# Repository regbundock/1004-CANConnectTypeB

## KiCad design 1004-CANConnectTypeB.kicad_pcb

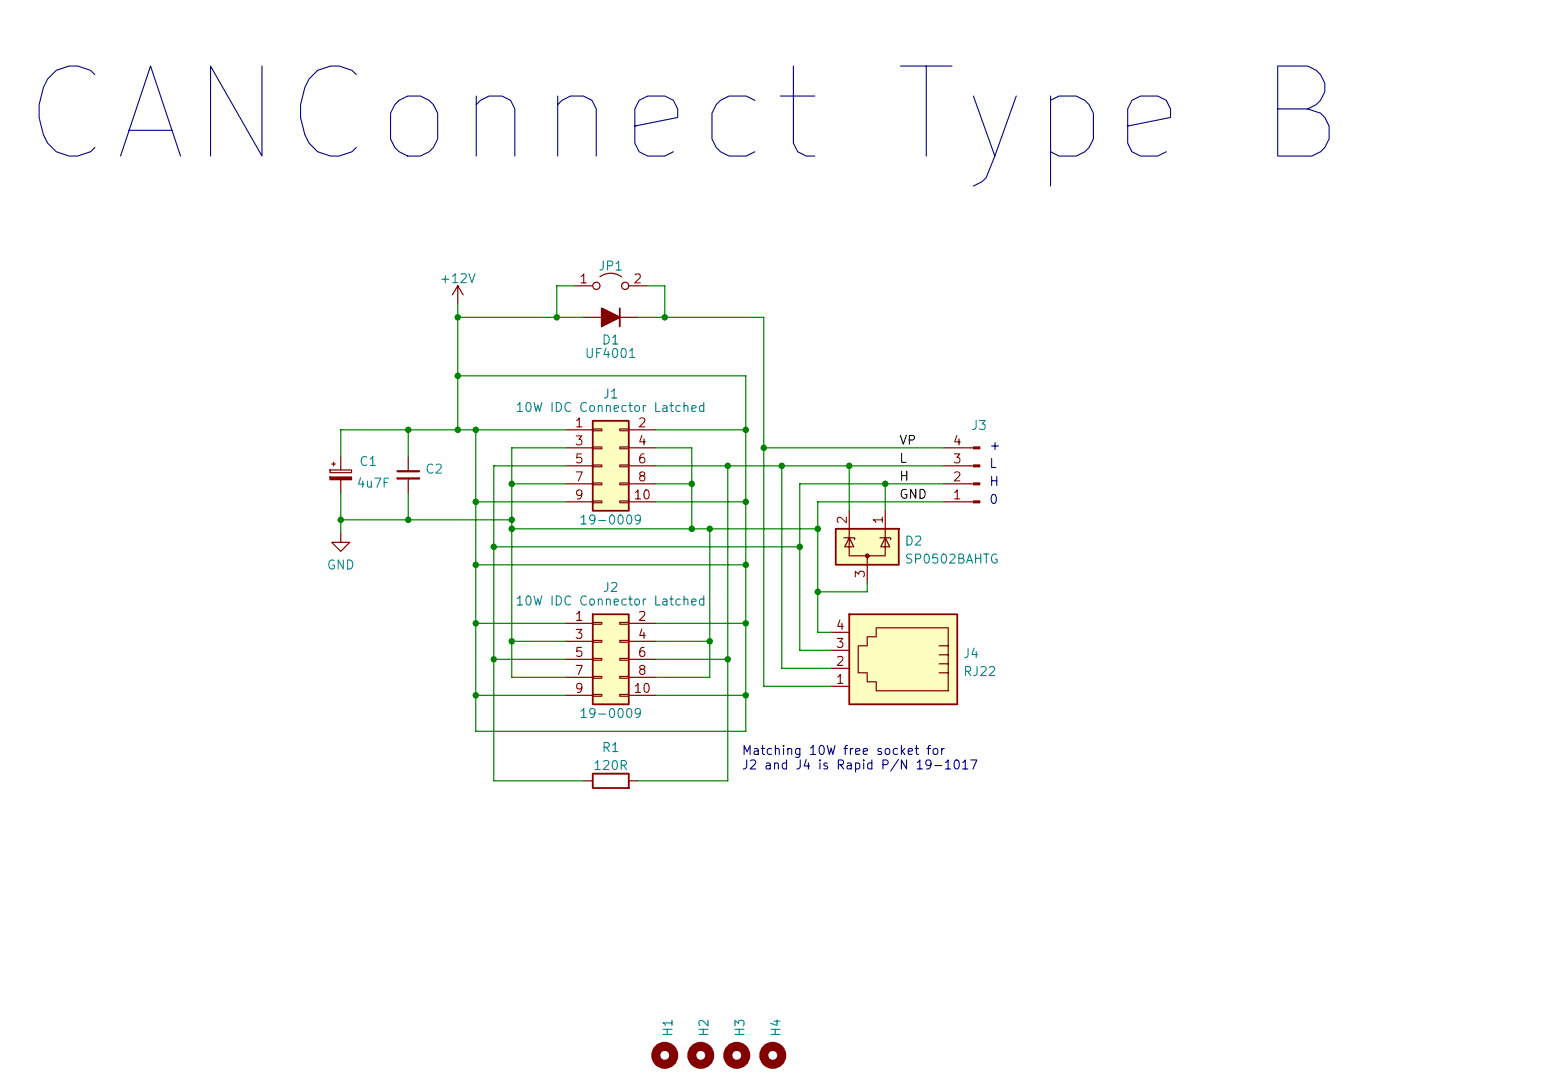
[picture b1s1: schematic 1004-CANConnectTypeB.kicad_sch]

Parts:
C1: 4u7F; CP_Radial_Tantal_D4.5mm_P2.50mm
C2: C_Disc_D4.7mm_W2.5mm_P5.00mm
D1: UF4001; D_DO-41_SOD81_P10.16mm_Horizontal
D2: SP0502BAHTG; SOT-23
H1, H2, H3, H4: MountingHole_3.2mm_M3_DIN965_Pad_TopBottom
J1, J2: 10W IDC Connector Latched; IDC-Header_2x05_P2.54mm_Latch_Vertical; Part No. 19-0009
J3: Camdenboss_3pt5mm_pitch_PCB_horizontal_4Way
J4: RJ22
JP1: PinHeader_1x02_P2.54mm_Vertical
R1: 120R; R_Axial_DIN0207_L6.3mm_D2.5mm_P10.16mm_Horizontal

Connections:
+12V: C1.1, C2.1, D1.2 (A), J1.1, J1.2, J1.9, J1.10, J2.1, J2.2, J2.9, J2.10, JP1.1 (A)
/H: D2.1 (K), J1.5, J2.5, J3.2, J4.3, R1.1
/L: D2.2 (K), J1.6, J2.6, J3.3, J4.2, R1.2
/VP: D1.1 (K), J3.4, J4.1, JP1.2 (B)
GND: C1.2, C2.2, D2.3 (A), J1.3, J1.4, J1.7, J1.8, J2.3, J2.4, J2.7, J2.8, J3.1, J4.4

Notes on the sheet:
CANConnect Type B
Matching 10W free socket for J2 and J4 is Rapid P/N 19-1017

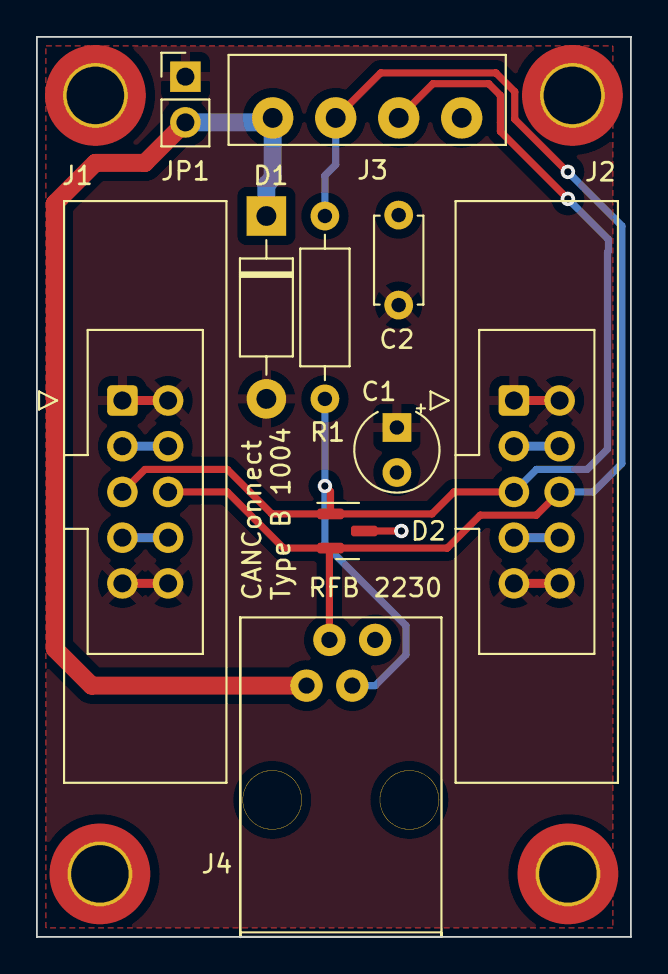
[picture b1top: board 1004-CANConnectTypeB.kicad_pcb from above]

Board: 2 copper layers, 33.0 x 50.0 mm, 14 parts (0 on the bottom side), 5 nets.

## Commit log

2022-09-17 forst commit
